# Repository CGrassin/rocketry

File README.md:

# Charleslab's rocketery

Thrust vectoring is the ability of an aircraft, rocket, or other vehicle to manipulate the direction of the thrust from its motor in order to control the attitude (angle) of the vehicle. It is used in rocketry it is the primary means of attitude control, as aerodynamic control surfaces are ineffective outside the atmosphere.

This repository contains all resources for my model rocketery experiments. The content of each folder is described hereunder.

Everything is work in progress (currently working on the code and the gimbal).

## 3D models

This folder contains the 3D models for my rocket:
* The 2 axes thrust vectoring control (TVC) gimbal (SolidWorks),
* The gimbal test stand (OpenSCAD parametric design),
* The PCB holder (OpenSCAD parametric design),
* The nose cone (OpenSCAD parametric design).

TODO : add render of all models

The gimbal is a 3D-printable, parametric Solidworks model. There are two variables that should be adjusted to fit your needs: the diameter of the rocket motor and the diameter of the rocket body. The geometry adapts to these constraints. It should be 3D-printed with supports enabled.

TODO : add photo

The cone is a work-in-progress parametric openSCAD model.

## Electronics

The "Sagan" PCB is my rocket's onboard computer. It features:
* Arduino Mini (ATMega328P at 3.3v),
* BMP280 barometer,
* MPU6050 gyroscope and accelerometer,
* Micro SD Card reader to store in-flight telemetry,
* 3 servo outputs (X, Y and extra),
* 2 pyro channels (PYRO0 and PYRO1),
* LED and buzzer.

TODO : add picture

Designed in KiCad.

## Code

This folder contains the Arduino code for the "Sagan" PCB.

To tune and test the controller, I made a Java gimbaled rocket simulator: http://charleslabs.fr/en/project-Gimbaled+Model+Rocket+Simulator

## Flight data

This folder holds the data (telemetry) for each flight of the rocket.

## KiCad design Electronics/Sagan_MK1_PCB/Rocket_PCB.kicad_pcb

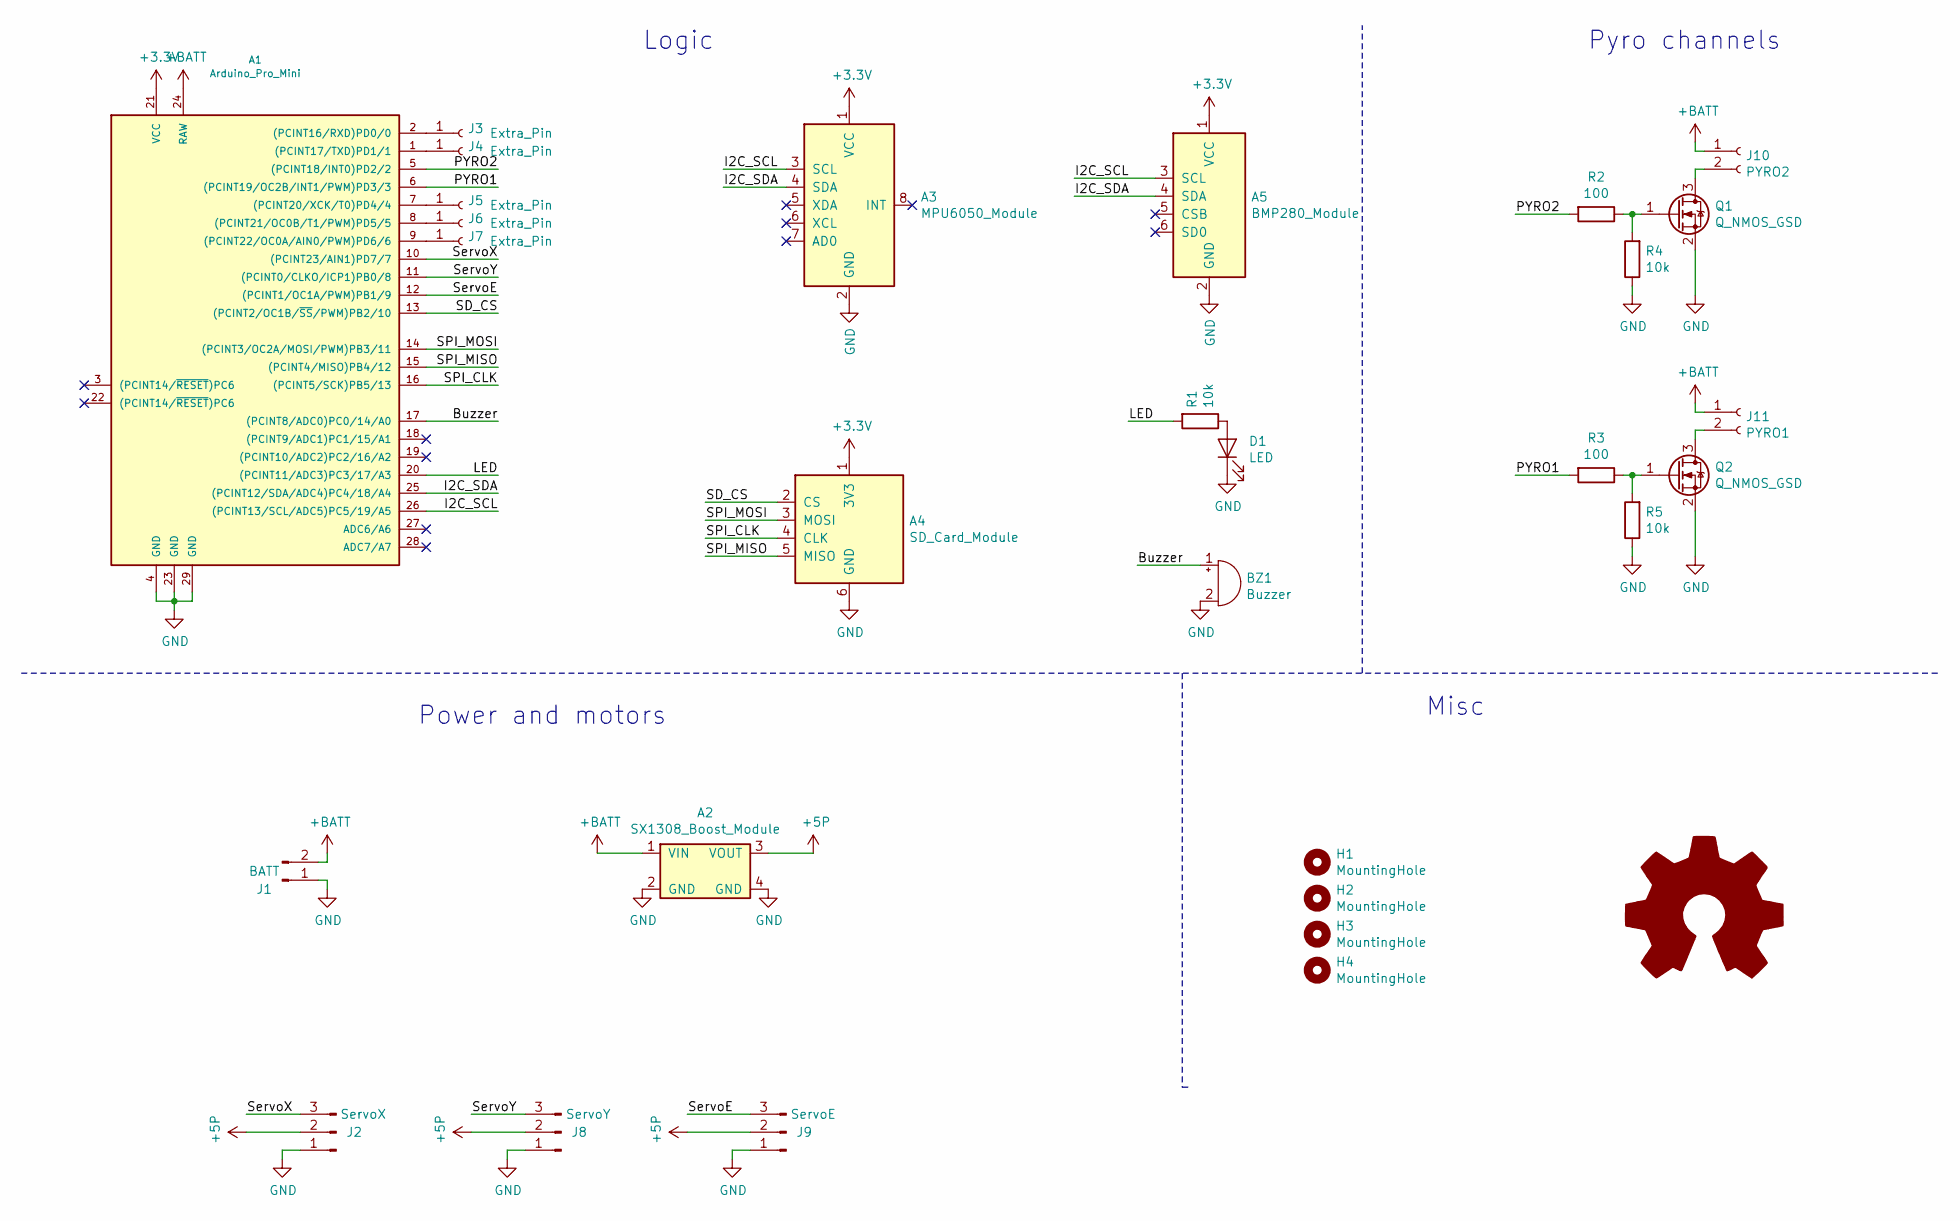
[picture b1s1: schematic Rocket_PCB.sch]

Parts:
A1: Arduino_Pro_Mini; Arduino_Pro_Mini_China
A2: SX1308_Boost_Module
A3: MPU6050_Module
A4: SD_Card_Module
A5: BMP280_Module
BZ1: Buzzer; Buzzer_12x9.5RM7.6
D1: LED; LED_0805_2012Metric
H1, H2, H3, H4: MountingHole; MountingHole_3.2mm_M3
J1: BATT; PinHeader_1x02_P2.54mm_Vertical
J2: ServoX; PinHeader_1x03_P2.54mm_Vertical
J3, J4, J5, J6, J7: Extra_Pin; PinHeader_1x01_P2.54mm_Vertical
J8: ServoY; PinHeader_1x03_P2.54mm_Vertical
J9: ServoE; PinHeader_1x03_P2.54mm_Vertical
J10: PYRO2; TerminalBlock_TE_282834-2_1x02_P2.54mm_Horizontal
J11: PYRO1; TerminalBlock_TE_282834-2_1x02_P2.54mm_Horizontal
LOGO1: Logo_Open_Hardware_Large; Charleslabs_Logo_5mm
Q1, Q2: Q_NMOS_GSD; SOT-23
R1, R4, R5: 10k; R_0805_2012Metric
R2, R3: 100; R_0805_2012Metric

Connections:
+3V3: A1.21 (VCC), A3.1 (VCC), A4.1 (3V3), A5.1 (VCC)
+5P: A2.3 (VOUT), J2.2, J8.2, J9.2
+BATT: A1.24 (RAW), A2.1 (VIN), J1.2, J10.1, J11.1
/Buzzer: A1.17 ((PCINT8/ADC0)PC0/14/A0), BZ1.1 (-)
/I2C_SCL: A1.26 ((PCINT13/SCL/ADC5)PC5/19/A5), A3.3 (SCL), A5.3 (SCL)
/I2C_SDA: A1.25 ((PCINT12/SDA/ADC4)PC4/18/A4), A3.4 (SDA), A5.4 (SDA)
/LED: A1.20 ((PCINT11/ADC3)PC3/17/A3), R1.2
/PYRO1: A1.6 ((PCINT19/OC2B/INT1/PWM)PD3/3), R3.2
/PYRO2: A1.5 ((PCINT18/INT0)PD2/2), R2.2
/SD_CS: A1.13 ((PCINT2/OC1B/~SS~/PWM)PB2/10), A4.2 (CS)
/SPI_CLK: A1.16 ((PCINT5/SCK)PB5/13), A4.4 (CLK)
/SPI_MISO: A1.15 ((PCINT4/MISO)PB4/12), A4.5 (MISO)
/SPI_MOSI: A1.14 ((PCINT3/OC2A/MOSI/PWM)PB3/11), A4.3 (MOSI)
/ServoE: A1.12 ((PCINT1/OC1A/PWM)PB1/9), J9.3
/ServoX: A1.10 ((PCINT23/AIN1)PD7/7), J2.3
/ServoY: A1.11 ((PCINT0/CLKO/ICP1)PB0/8), J8.3
GND: A1.4 (GND), A1.23 (GND), A1.29 (GND), A2.2 (GND), A2.4 (GND), A3.2 (GND), A4.6 (GND), A5.2 (GND), BZ1.2 (+), D1.1 (K), J1.1, J2.1, J8.1, J9.1, Q1.2 (S), Q2.2 (S), R4.1, R5.1
unnamed: A1.1 ((PCINT17/TXD)PD1/1), J4.1
unnamed: A1.2 ((PCINT16/RXD)PD0/0), J3.1
unnamed: A1.7 ((PCINT20/XCK/T0)PD4/4), J5.1
unnamed: A1.8 ((PCINT21/OC0B/T1/PWM)PD5/5), J6.1
unnamed: A1.9 ((PCINT22/OC0A/AIN0/PWM)PD6/6), J7.1
unnamed: D1.2 (A), R1.1
unnamed: J10.2, Q1.3 (D)
unnamed: J11.2, Q2.3 (D)
unnamed: Q1.1 (G), R2.1, R4.2
unnamed: Q2.1 (G), R3.1, R5.2

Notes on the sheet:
Logic
Pyro channels
Power and motors
Misc

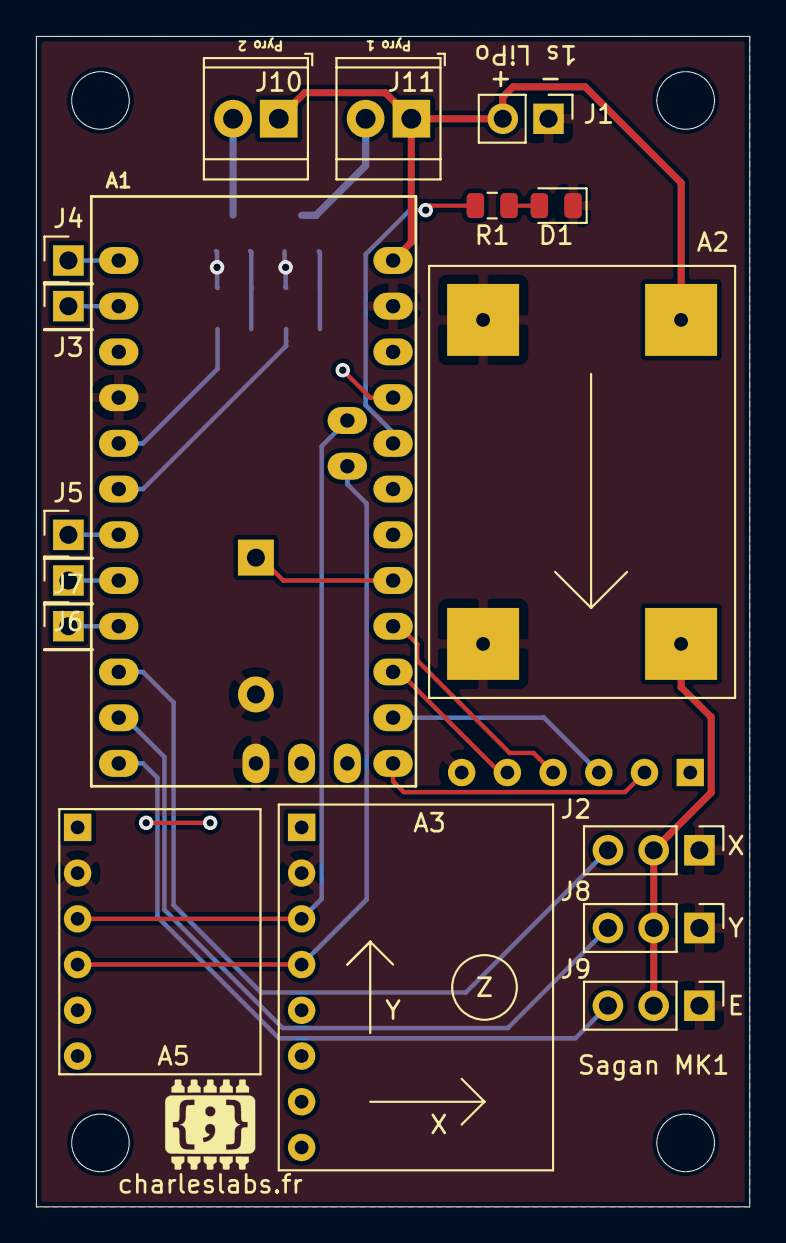
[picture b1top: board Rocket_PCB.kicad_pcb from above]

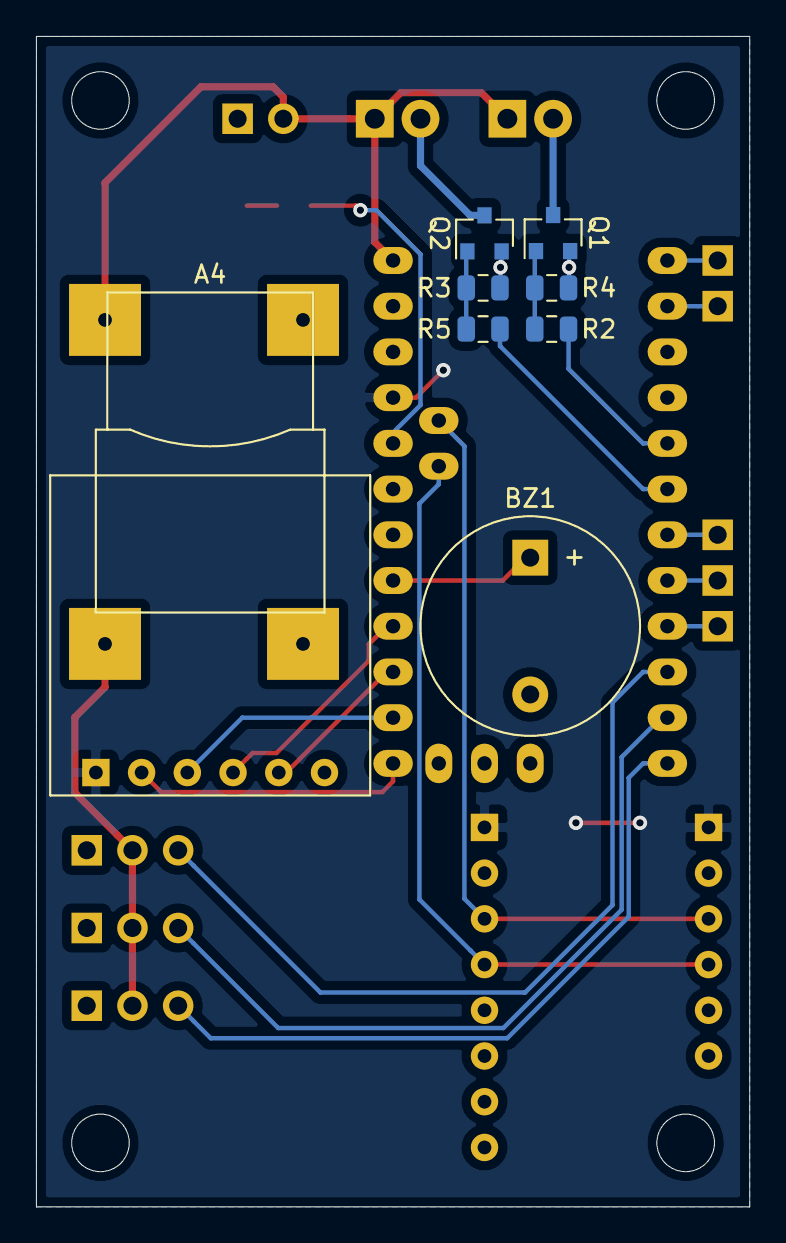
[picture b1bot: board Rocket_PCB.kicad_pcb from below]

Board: 2 copper layers, 39.6 x 65.0 mm, 30 parts (8 on the bottom side), 27 nets.

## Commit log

2020-03-03 Replaced PCB holder with OpenSCAD model
2020-03-04 Improved PCB holder model
2020-03-05 Added OpenSCAD gimbal test stand
